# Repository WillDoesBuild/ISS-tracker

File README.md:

# ISS-tracker
A physical ISS tracker that moves a model of the International Space Station around a globe using magnets. Uses an ESP32 to update the ISS location every 15 seconds from the Open Notify API. Here's a video about it!  (https://youtu.be/nbEe-BCNutg)

This GitHub repo only serves to hold files. Please see the Instructable about it here! (https://www.instructables.com/DIY-International-Space-Station-Tracker/)

<a href="https://creativecommons.org">ISS tracker</a> © 2025 by <a href="https://creativecommons.org">Will Dana</a> is licensed under <a href="https://creativecommons.org/licenses/by-nc-sa/4.0/">CC BY-NC-SA 4.0</a>

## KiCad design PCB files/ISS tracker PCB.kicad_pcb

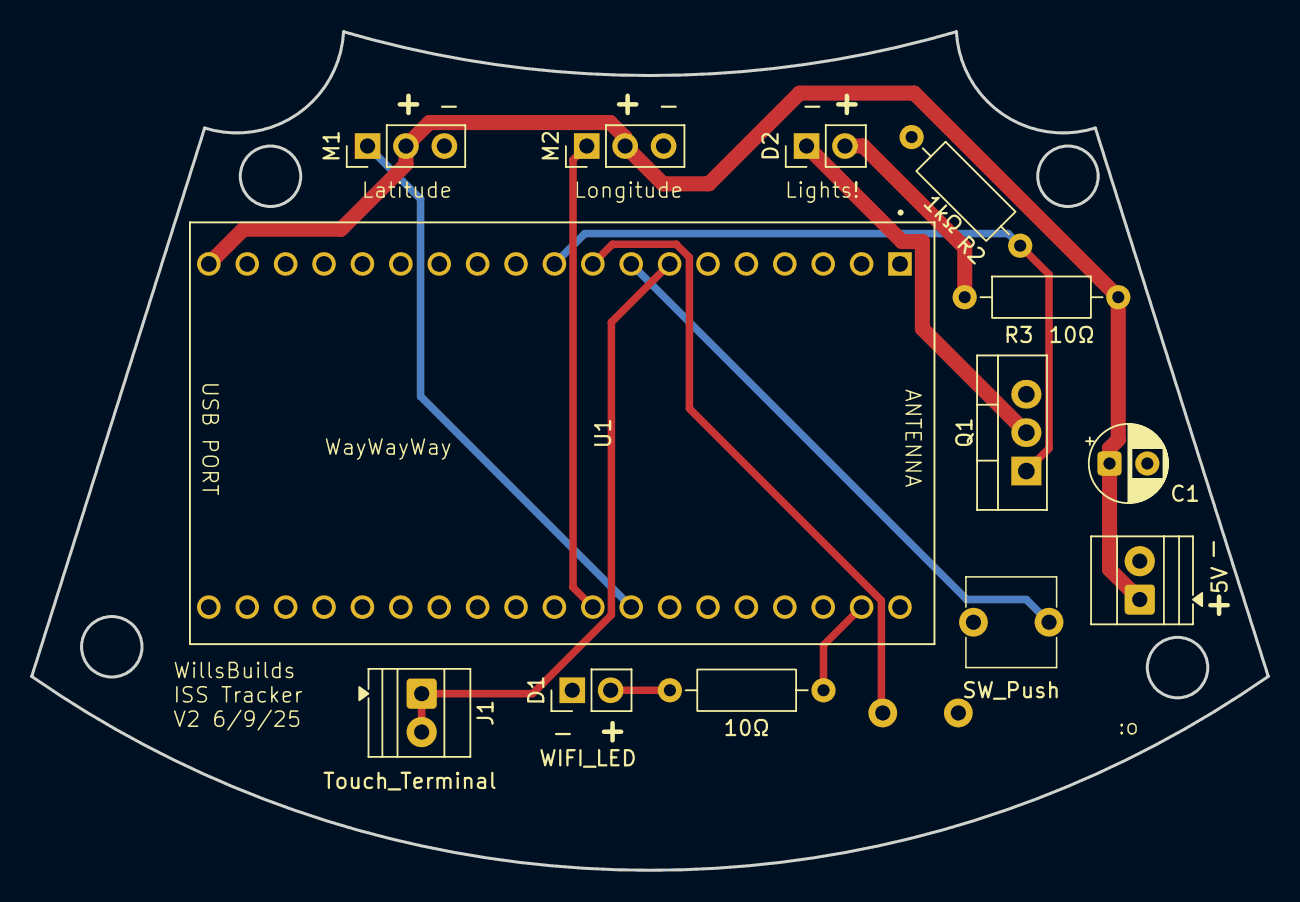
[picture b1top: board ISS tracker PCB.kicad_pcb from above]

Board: 2 copper layers, 81.8 x 55.5 mm, 14 parts (1 on the bottom side), 12 nets.

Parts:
BT1: 5V; TerminalBlock_Xinya_XY308-2.54-2P_1x02_P2.54mm_Horizontal
C1: C; CP_Radial_D5.0mm_P2.50mm
D1: WIFI_LED; PinHeader_1x02_P2.54mm_Vertical
D2: LAMP_PARALLEL_LEDS; PinHeader_1x02_P2.54mm_Vertical
J1: Touch_Terminal; TerminalBlock_Xinya_XY308-2.54-2P_1x02_P2.54mm_Horizontal
M1: Long_Servo; PinHeader_1x03_P2.54mm_Vertical
M2: Lat_Servo; PinHeader_1x03_P2.54mm_Vertical
Q1: IRF540N; TO-220-3_Vertical
R1, R3: 10Ω; R_Axial_DIN0207_L6.3mm_D2.5mm_P10.16mm_Horizontal
R2: 1kΩ; R_Axial_DIN0207_L6.3mm_D2.5mm_P10.16mm_Horizontal
SW1: Calibrate; QTEATAK pushbutton
SW2: SW_Push; QTEATAK pushbutton
U1: ESP32-DEVKITC-32D; FIXEDMODULE_ESP32-DEVKITC-32D

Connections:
unnamed: BT1.1 (+), C1.1, M1.2 (+), M2.2 (+), R3.2, U1.J2-19 (EXT_5V)
unnamed: BT1.2 (-), C1.2, D1.1 (K), M1.3 (-), M2.3 (-), Q1.3 (S), R2.1, SW1.1, SW2.1, U1.J2-14 (GND1), U1.J3-1 (GND3)
unnamed: D1.2 (A), R1.2
unnamed: D2.2 (A), R3.1
unnamed: D2.1 (K), Q1.2 (D)
unnamed: J1.1, J1.2, U1.J2-7 (IO32)
unnamed: M1.1 (PWM), U1.J3-8 (IO19)
unnamed: M2.1 (PWM), U1.J3-9 (IO18)
unnamed: Q1.1 (G), R2.2, U1.J2-10 (IO26)
unnamed: R1.1, U1.J3-2 (IO23)
unnamed: SW1.2, U1.J2-9 (IO25)
unnamed: SW2.2, U1.J2-8 (IO33)
